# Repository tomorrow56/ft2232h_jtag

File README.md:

## FT2232HL JTAG Adapter

### Function

Can be used as Xilinx JTAG downloader & USB-to-UART bridge simultaneously following [this](https://gist.github.com/rikka0w0/24b58b54473227502fa0334bbe75c3c1).

Partly pin-to-pin compatible with the CJMCU FT232HL(the purple PCB one) and has a standard 2x7 JTAG connector.

Main chips: FT2232HL(QFP64), ASM1117(3.3V, SOT89), 93LC56(SOP8).

Type-C(tested later so not shown on pic) connection.

Made with Kicad 10.0.

---
以下の手順に従い、EEPROMにデータを書き込むことで、Xilinx JTAG ダウンローダーと USB-UART ブリッジとして同時に使用できます。

```PowerShell
cd <Vivado install dir>\bin\
.\program_ftdi.bat -write -ftdi FT2232H -serial FT000001 -vendor "Your Name" -board "FT2232H-JTAG" -desc "FT2232H JTAG Adapter"
```

* 標準的な2.54mmピッチの 2x7 JTAGコネクタと 1x4 UARTコネクタを搭載しています
* 主要チップ: FT2232HL(QFP64)、ASM1117(3.3V, SOT89)、93LC56(SOP8)
* Type-C コネクタ搭載

#### 設計環境
KiCad 10.0 で設計

#### Gallery

#### License

GPL-v3

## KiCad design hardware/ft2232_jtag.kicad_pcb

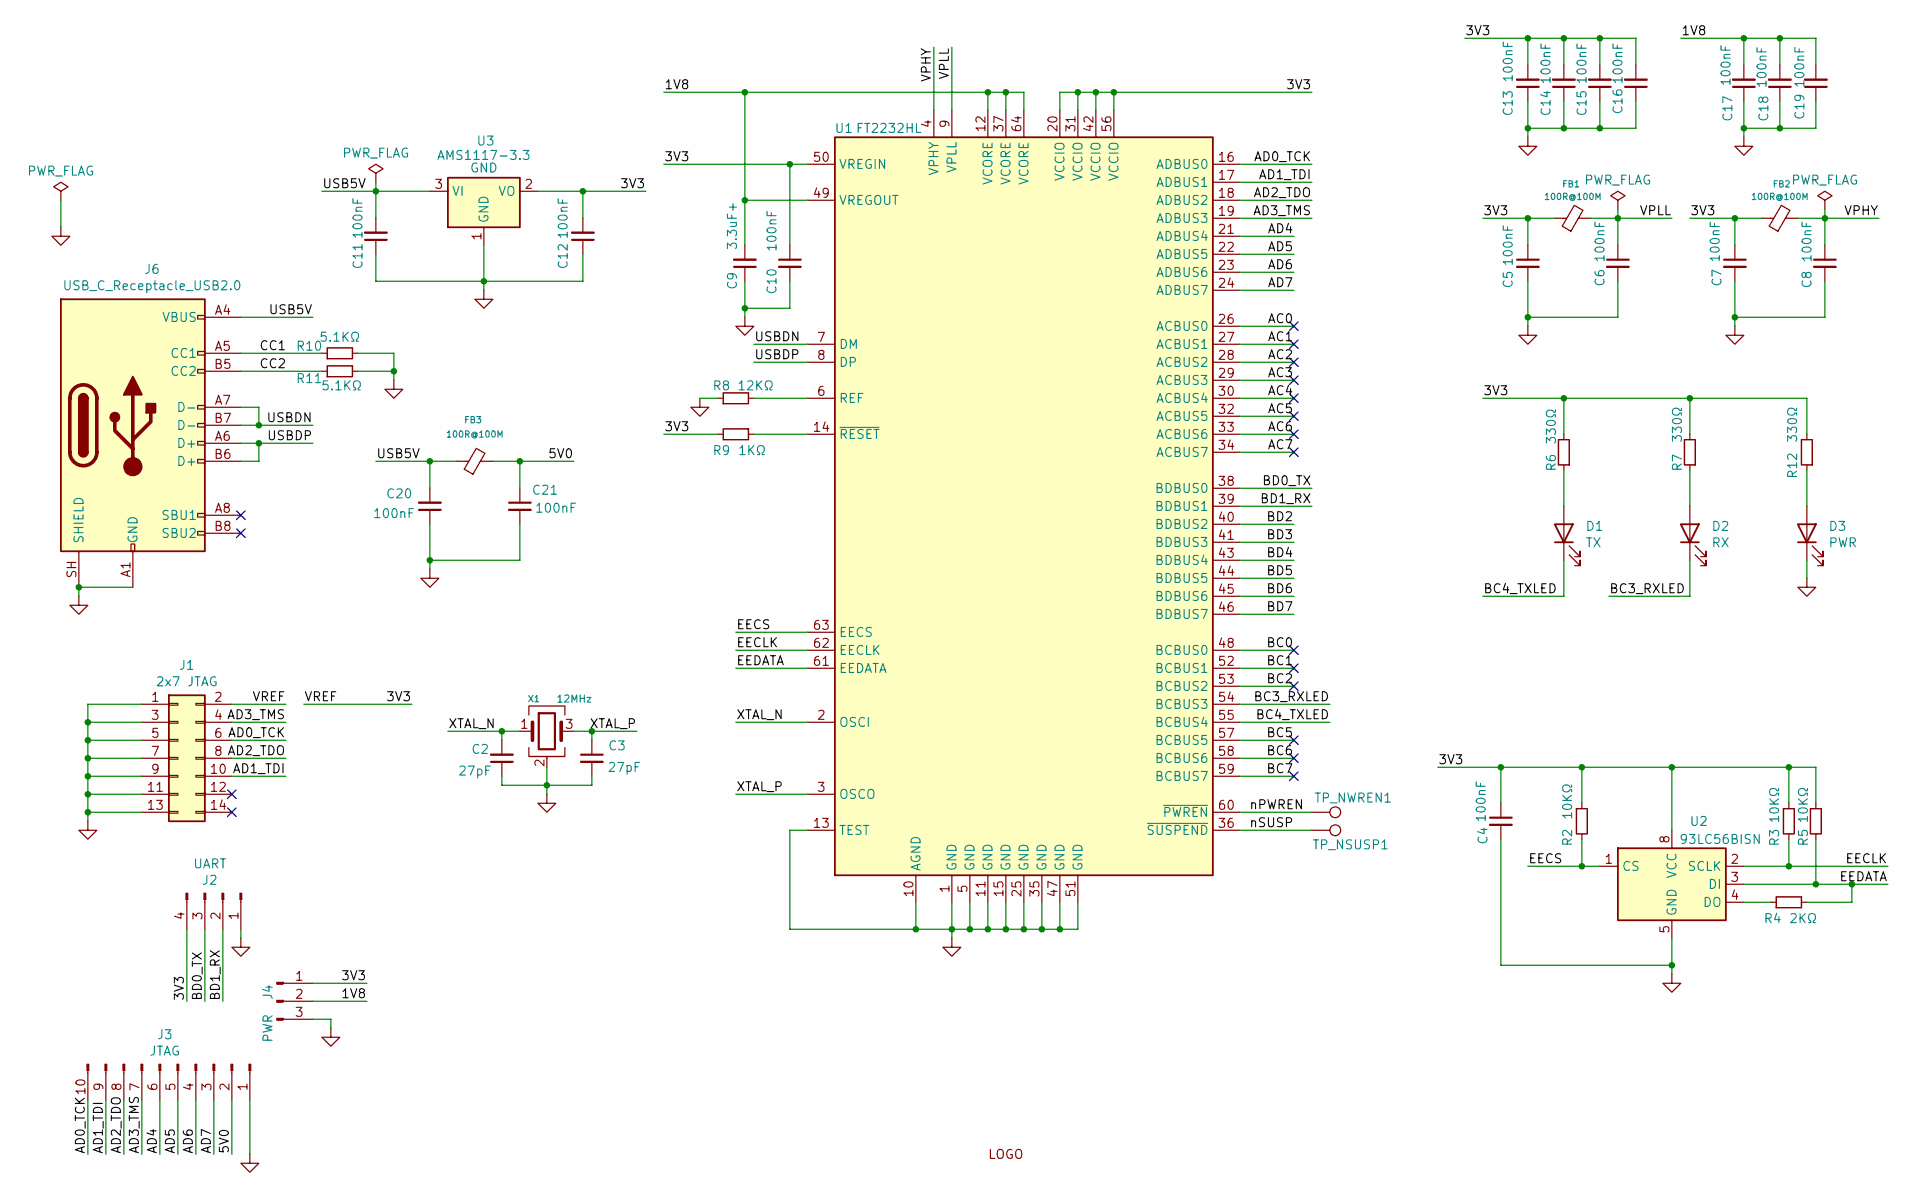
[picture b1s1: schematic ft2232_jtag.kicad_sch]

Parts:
C2, C3: 0805_27pF__270_5%_50V; C_0603_1608Metric
C4, C5, C6, C7, C8, C10, C11, C12, C13, C14, C15, C16, C17, C18, C19, C20, C21: 1206_100nF__104_10%_50V; C_0603_1608Metric
C9: 0805_3.3nF__332_10%_50V; C_0603_1608Metric
D1: TX; LED_0603_1608Metric
D2: RX; LED_0603_1608Metric
D3: PWR; LED_0603_1608Metric
FB1, FB2, FB3: 100R@100M; L_0603_1608Metric
J1: 2x7 JTAG; PinHeader_2x07_P2.54mm_Vertical
J2: UART; PinHeader_1x04_P2.54mm_Vertical
J3: JTAG; PinHeader_1x10_P2.54mm_Vertical
J4: PWR; PinHeader_1x03_P2.54mm_Vertical
J6: USB_C_Receptacle_USB2.0; USB_C_Receptacle_HRO_TYPE-C-31-M-12
R2, R3, R5: 1206_10KΩ__1002_1%; R_0603_1608Metric
R4: 1206_2KΩ__2001_1%; R_0603_1608Metric
R6, R7, R12: 0805_330Ω__3300_1%; R_0603_1608Metric
R8: 0805_12KΩ__1202_1%; R_0603_1608Metric
R9: 1206_1KΩ__1001_1%; R_0603_1608Metric
R10, R11: 0805_5.1KΩ__5101_1%; R_0603_1608Metric
TP_NSUSP1: VALUE; TestPoint_Pad_D1.0mm
TP_NWREN1: VALUE; TestPoint_Pad_D1.0mm
U1: FT2232HL; LQFP-64_10x10mm_P0.5mm
U2: 93LC56BISN; JEITA_SOIC-8_3.9x4.9mm_P1.27mm
U3: SOT-223_AMS1117-3.3; SOT-223-3_TabPin2
X1: 12MHz; Crystal_SMD_3225-4Pin_3.2x2.5mm
logo1: Logo_undefined; TDIY-LOGO-S

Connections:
/1V8: C9.2, C17.2, C18.2, C19.2, J4.2, U1.12 (VCORE), U1.37 (VCORE), U1.49 (VREGOUT), U1.64 (VCORE)
/3V3: C4.1, C5.1, C7.1, C10.1, C12.2, C13.2, C14.2, C15.2, C16.2, FB1.1, FB2.1, J1.2, J2.4, J4.1, R2.1, R3.1, R5.1, R6.2, R7.2, R9.2, R12.2, U1.20 (VCCIO), U1.31 (VCCIO), U1.42 (VCCIO), U1.50 (VREGIN), U1.56 (VCCIO), U2.8 (VCC), U3.2 (VO)
/5V0: C21.1, FB3.2, J3.2
/AC0: U1.26 (ACBUS0)
/AC1: U1.27 (ACBUS1)
/AC2: U1.28 (ACBUS2)
/AC3: U1.29 (ACBUS3)
/AC4: U1.30 (ACBUS4)
/AC5: U1.32 (ACBUS5)
/AC6: U1.33 (ACBUS6)
/AC7: U1.34 (ACBUS7)
/AD0_TCK: J1.6, J3.10, U1.16 (ADBUS0)
/AD1_TDI: J1.10, J3.9, U1.17 (ADBUS1)
/AD2_TDO: J1.8, J3.8, U1.18 (ADBUS2)
/AD3_TMS: J1.4, J3.7, U1.19 (ADBUS3)
/AD4: J3.6, U1.21 (ADBUS4)
/AD5: J3.5, U1.22 (ADBUS5)
/AD6: J3.4, U1.23 (ADBUS6)
/AD7: J3.3, U1.24 (ADBUS7)
/BC0: U1.48 (BCBUS0)
/BC1: U1.52 (BCBUS1)
/BC2: U1.53 (BCBUS2)
/BC3_RXLED: D2.1 (K), U1.54 (BCBUS3)
/BC4_TXLED: D1.1 (K), U1.55 (BCBUS4)
/BC5: U1.57 (BCBUS5)
/BC6: U1.58 (BCBUS6)
/BC7: U1.59 (BCBUS7)
/BD0_TX: J2.3, U1.38 (BDBUS0)
/BD1_RX: J2.2, U1.39 (BDBUS1)
/BD2: U1.40 (BDBUS2)
/BD3: U1.41 (BDBUS3)
/BD4: U1.43 (BDBUS4)
/BD5: U1.44 (BDBUS5)
/BD6: U1.45 (BDBUS6)
/BD7: U1.46 (BDBUS7)
/CC1: J6.A5 (CC1), R10.1
/CC2: J6.B5 (CC2), R11.1
/EECLK: R3.2, U1.62 (EECLK), U2.2 (SCLK)
/EECS: R2.2, U1.63 (EECS), U2.1 (CS)
/EEDATA: R4.2, R5.2, U1.61 (EEDATA), U2.3 (DI)
/USB5V: C11.2, C20.2, FB3.1, J6.A4 (VBUS), J6.A9 (VBUS), J6.B4 (VBUS), J6.B9 (VBUS), U3.3 (VI)
/USBDN: J6.A7 (D-), J6.B7 (D-), U1.7 (DM)
/USBDP: J6.A6 (D+), J6.B6 (D+), U1.8 (DP)
/VPHY: C8.1, FB2.2, U1.4 (VPHY)
/VPLL: C6.1, FB1.2, U1.9 (VPLL)
/XTAL_N: C2.2, U1.2 (OSCI), X1.1
/XTAL_P: C3.1, U1.3 (OSCO), X1.3
/nPWREN: TP_NWREN1.1 (1_1), U1.60 (~PWREN)
/nSUSP: TP_NSUSP1.1 (1_1), U1.36 (~SUSPEND)
GND: C2.1, C3.2, C4.2, C5.2, C6.2, C7.2, C8.2, C9.1, C10.2, C11.1, C12.1, C13.1, C14.1, C15.1, C16.1, C17.1, C18.1, C19.1, C20.1, C21.2, D3.1 (K), J1.1, J1.3, J1.5, J1.7, J1.9, J1.11, J1.13, J2.1, J3.1, J4.3, J6.A1 (GND), J6.A12 (GND), J6.B1 (GND), J6.B12 (GND), J6.SH (SHIELD), R8.1, R10.2, R11.2, U1.1 (GND), U1.5 (GND), U1.10 (AGND), U1.11 (GND), U1.13 (TEST), U1.15 (GND), U1.25 (GND), U1.35 (GND), U1.47 (GND), U1.51 (GND), U2.5 (GND), U3.1 (GND), X1.2 (G), X1.4 (G)
unnamed: D1.2 (A), R6.1
unnamed: D2.2 (A), R7.1
unnamed: D3.2 (A), R12.1
unnamed: R8.2, U1.6 (REF)
unnamed: R9.1, U1.14 (~RESET)
unnamed: R4.1, U2.4 (DO)

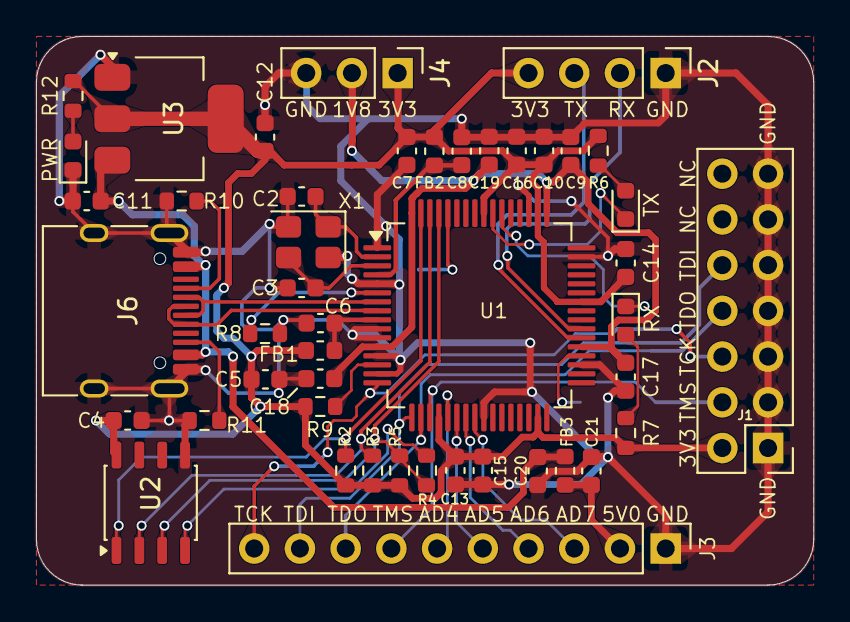
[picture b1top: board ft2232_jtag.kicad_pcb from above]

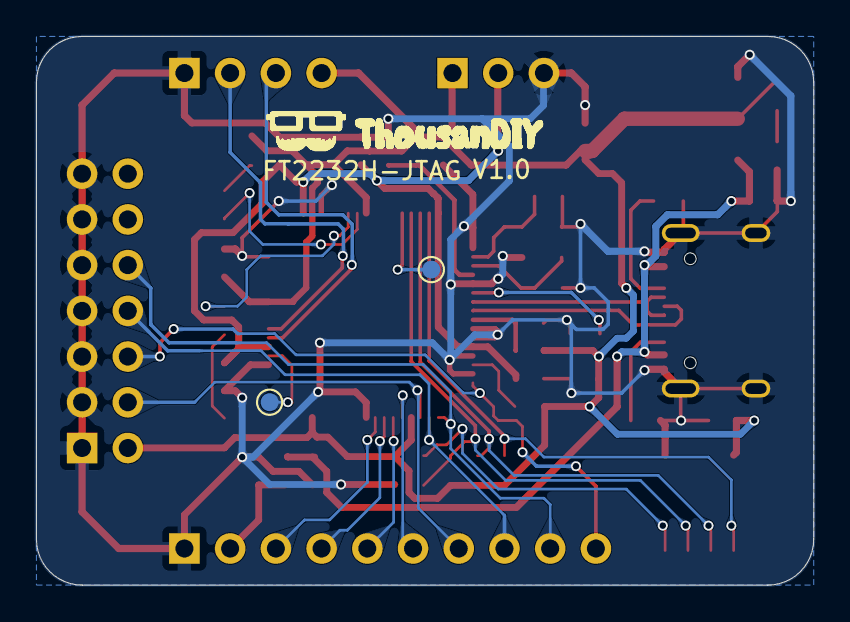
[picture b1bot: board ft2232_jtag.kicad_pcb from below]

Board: 2 copper layers, 43.2 x 30.5 mm, 49 parts (3 on the bottom side), 36 nets.

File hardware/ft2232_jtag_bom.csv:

"ID";"指定子";"フットプリント";"数量";"名称";"供給業者、参考資料";
1;"C2, C3";"C_0603_1608Metric";2;"0805_27pF__270_5%_50V";;;
2;"C4, C5, C6, C7, C8, C10, C11, C12, C13, C14, C15, C16, C17, C18, C19, C20, C21";"C_0603_1608Metric";17;"1206_100nF__104_10%_50V";;;
3;"C9";"C_0603_1608Metric";1;"0805_3.3nF__332_10%_50V";;;
4;"D1";"LED_0603_1608Metric";1;"TX";;;
5;"D2";"LED_0603_1608Metric";1;"RX";;;
6;"D3";"LED_0603_1608Metric";1;"PWR";;;
7;"FB1, FB2, FB3";"L_0603_1608Metric";3;"100R@100M";;;
8;"J1";"PinHeader_2x07_P2.54mm_Vertical";1;"2x7 JTAG";;;
9;"J2";"PinHeader_1x04_P2.54mm_Vertical";1;"UART";;;
10;"J3";"PinHeader_1x10_P2.54mm_Vertical";1;"JTAG";;;
11;"J4";"PinHeader_1x03_P2.54mm_Vertical";1;"PWR";;;
12;"J6";"USB_C_Receptacle_HRO_TYPE-C-31-M-12";1;"USB_C_Receptacle_USB2.0";;;
13;"logo1";"TDIY-LOGO-S";1;"Logo_undefined";;;
14;"R2, R3, R5";"R_0603_1608Metric";3;"1206_10KΩ__1002_1%";;;
15;"R4";"R_0603_1608Metric";1;"1206_2KΩ__2001_1%";;;
16;"R6, R7, R12";"R_0603_1608Metric";3;"0805_330Ω__3300_1%";;;
17;"R8";"R_0603_1608Metric";1;"0805_12KΩ__1202_1%";;;
18;"R9";"R_0603_1608Metric";1;"1206_1KΩ__1001_1%";;;
19;"R10, R11";"R_0603_1608Metric";2;"0805_5.1KΩ__5101_1%";;;
20;"TP_NSUSP1, TP_NWREN1";"TestPoint_Pad_D1.0mm";2;"VALUE";;;
21;"U1";"LQFP-64_10x10mm_P0.5mm";1;"FT2232HL";;;
22;"U2";"JEITA_SOIC-8_3.9x4.9mm_P1.27mm";1;"93LC56BISN";;;
23;"U3";"SOT-223-3_TabPin2";1;"SOT-223_AMS1117-3.3";;;
24;"X1";"Crystal_SMD_3225-4Pin_3.2x2.5mm";1;"12MHz";;;

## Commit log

2026-05-04 Add .gitignore and remove macOS junk files; update hardware files
2026-05-04 Add Japanese translation to Function section in README
2026-05-04 Remove macOS junk files; add hardware/lib and update files
2026-05-24 Update README with EEPROM usage instructions
    Added instructions for using EEPROM with Xilinx JTAG downloader and USB-UART bridge, including a PowerShell command example.
